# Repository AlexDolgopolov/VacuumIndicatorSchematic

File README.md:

<h1 align="center">Vacuum fluorescent clock</h1>
<h3 align="center">Vacuum fluorescent clock schematic and pcb. Drives with STM32F103 "BluePill". Driver code in progress.</h3>
<h4>Standart schematic for STM32F103 MCU. MCU pins connected to BJT's base with 4.7k resistors. VCC to heater and logic is 5V provided by external supply. I use the AP1117 LDO to make 
2.5 V heater voltage and VT1 for PWM the heater, drived from MCU. 3 button switches to provide user clock configuration, like setting timer or clock bright. Cathodes drived via npn BJT's.</h4>
<h2>
<h4>This scheme discribes anode drivers. I use +25 V Q=0.1..0.4 external voltage generator with simple schematic based on blocking genrator.
Schematic and PCB for this external generator will be added soon</h4>
<h2>
<h4>Connection between two PCB's realized by wires. If you open a PCB file in KiCAD, you can check the connections. Actually, it really doesn't matter how you connecting the wires, in STM32 driver you can remap the pins. But, PWM pins should be connected to heater.</h4>
<h2>
<h4>Thank you for watching this simple project. Work in progress now.</h4>

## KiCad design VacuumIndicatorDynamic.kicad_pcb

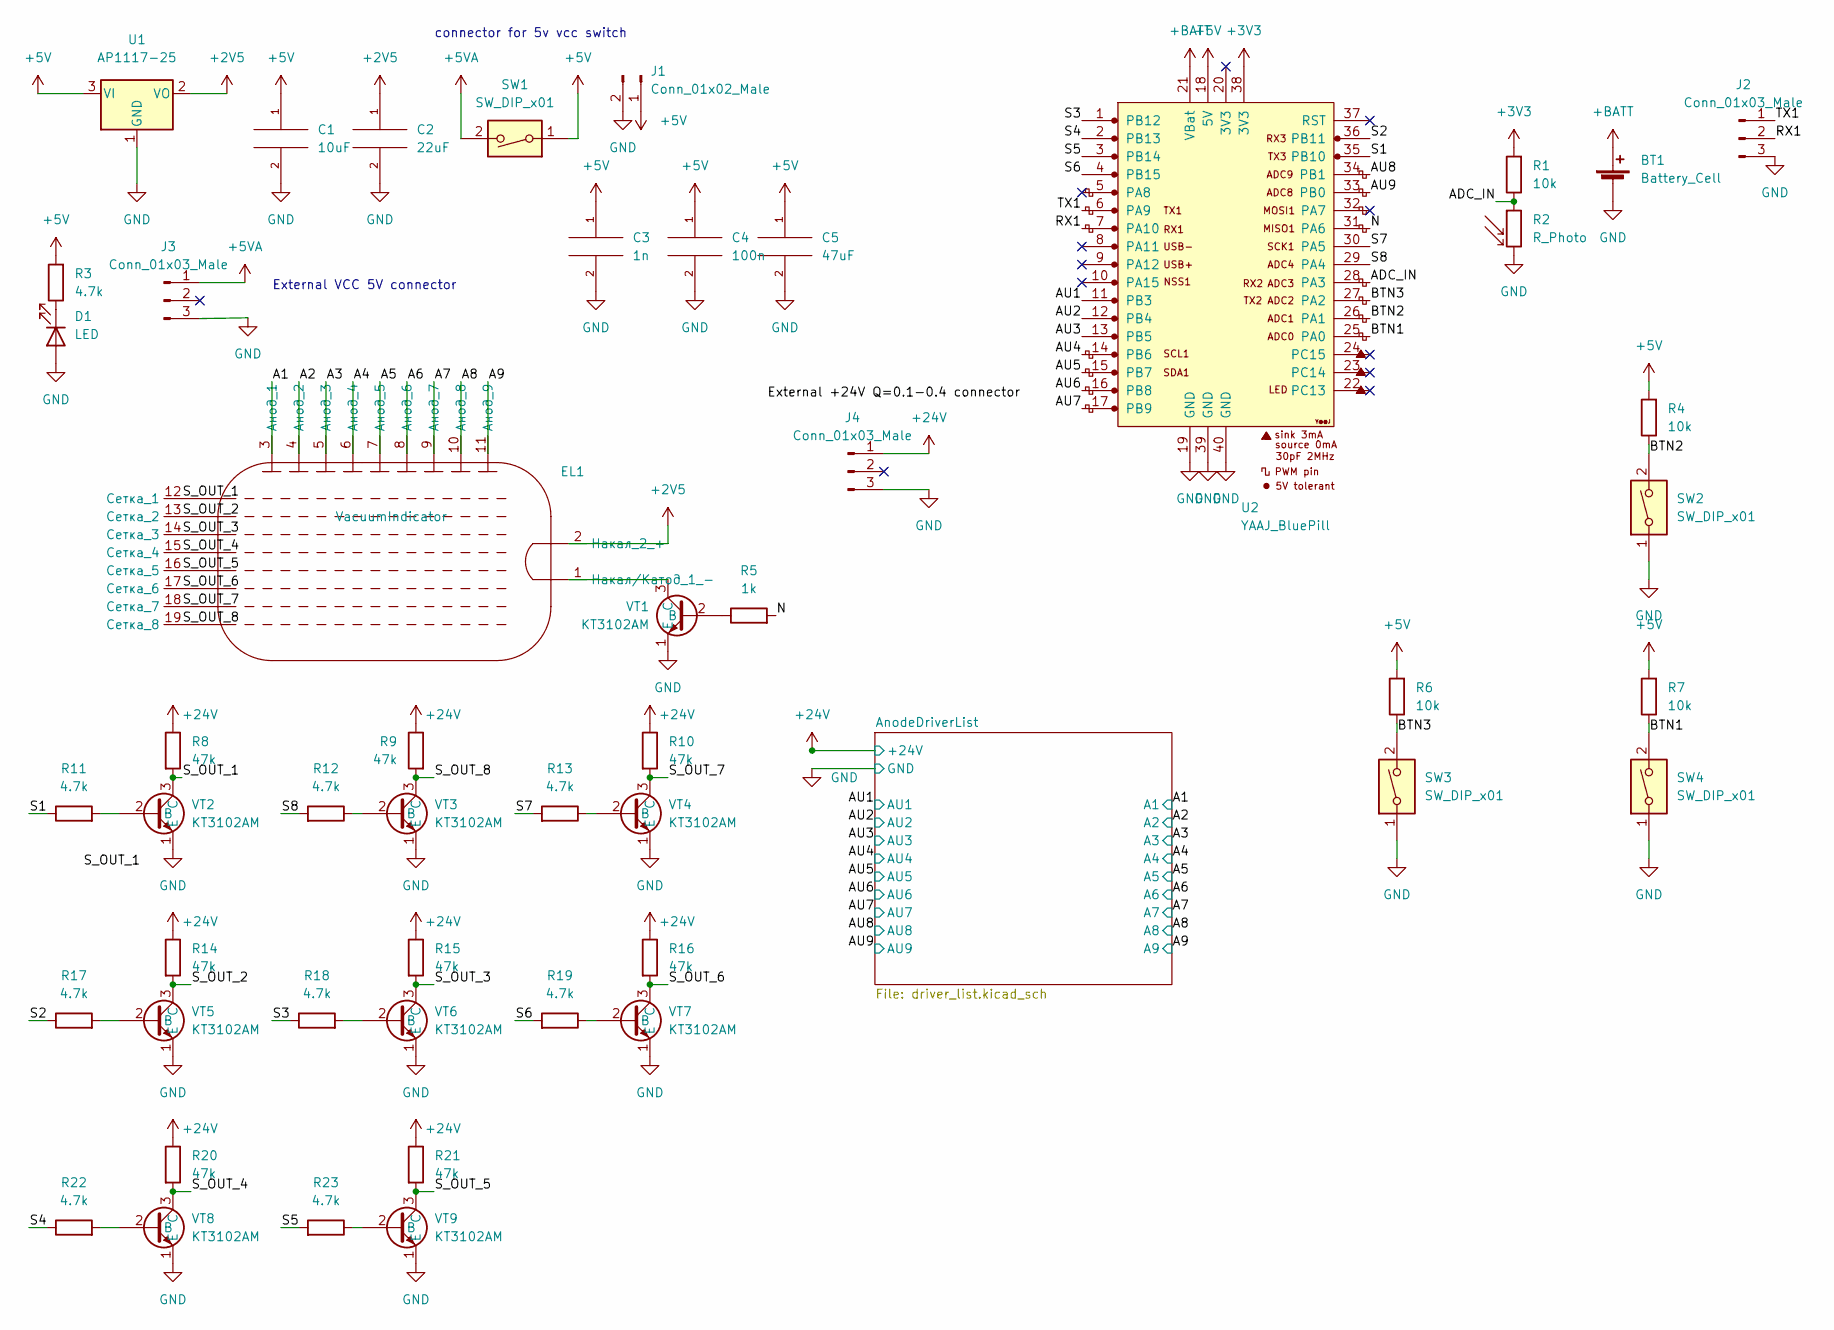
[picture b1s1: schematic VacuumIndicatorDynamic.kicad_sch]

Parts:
BT1: Battery_Cell; PinHeader_1x02_P2.54mm_Vertical
C1: 10uF; CP_Radial_D6.3mm_P2.50mm
C2: 22uF; CP_Radial_D6.3mm_P2.50mm
C3: 1n; C_0805_2012Metric
C4: 100n; C_0805_2012Metric
C5: 47uF; CP_Radial_D8.0mm_P5.00mm
D1: LED; LED_0805_2012Metric
EL1: VacuumIndicator; VauumIndicator_ILC_8-9
J1: Conn_01x02_Male; PinHeader_1x02_P2.54mm_Vertical
J2, J3, J4: Conn_01x03_Male; PinHeader_1x03_P2.54mm_Vertical
R1, R4, R6, R7: 10k; R_0805_2012Metric
R2: R_Photo; R_Axial_DIN0204_L3.6mm_D1.6mm_P1.90mm_Vertical
R3, R11, R12, R13, R17, R18, R19, R22, R23: 4.7k; R_0805_2012Metric
R5: 1k; R_0805_2012Metric
R8, R9, R10, R14, R15, R16, R20, R21: 47k; R_0805_2012Metric
SW1: SW_DIP_x01; PinSocket_1x02_P2.54mm_Vertical
SW2, SW3, SW4: SW_DIP_x01; SW_SPST_FSMSM
U1: AP1117-25; SOT-223-3_TabPin2
U2: YAAJ_BluePill; YAAJ_BluePill_1
VT1, VT2, VT3, VT4, VT5, VT6, VT7, VT8, VT9: KT3102AM; TO-92_HandSolder

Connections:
+2V5: C2.1, EL1.2 (Накал_2_+), U1.2 (VO)
+3V3: R1.2, U2.38 (3V3)
+5V: C1.1, C3.1, C4.1, C5.1, J1.1, R3.2, R4.2, R6.2, R7.2, SW1.1, U1.3 (VI), U2.18 (5V)
+5VA: J3.1, SW1.2
+24V: J4.1, R8.1, R9.1, R10.1, R14.1, R15.1, R16.1, R20.1, R21.1; also elsewhere on the board
+BATT: BT1.1 (+), U2.21 (VBat)
/A1: EL1.3 (Анод_1); also elsewhere on the board
/A2: EL1.4 (Анод_2); also elsewhere on the board
/A3: EL1.5 (Анод_3); also elsewhere on the board
/A4: EL1.6 (Анод_4); also elsewhere on the board
/A5: EL1.7 (Анод_5); also elsewhere on the board
/A6: EL1.8 (Анод_6); also elsewhere on the board
/A7: EL1.9 (Анод_7); also elsewhere on the board
/A8: EL1.10 (Анод_8); also elsewhere on the board
/A9: EL1.11 (Анод_9); also elsewhere on the board
/ADC_IN: R1.1, R2.1, U2.28 (PA3)
/AU1: U2.11 (PB3); also elsewhere on the board
/AU2: U2.12 (PB4); also elsewhere on the board
/AU3: U2.13 (PB5); also elsewhere on the board
/AU4: U2.14 (PB6); also elsewhere on the board
/AU5: U2.15 (PB7); also elsewhere on the board
/AU6: U2.16 (PB8); also elsewhere on the board
/AU7: U2.17 (PB9); also elsewhere on the board
/AU8: U2.34 (PB1); also elsewhere on the board
/AU9: U2.33 (PB0); also elsewhere on the board
/BTN1: R7.1, SW4.2, U2.25 (PA0)
/BTN2: R4.1, SW2.2, U2.26 (PA1)
/BTN3: R6.1, SW3.2, U2.27 (PA2)
/N: R5.2, U2.31 (PA6)
/RX1: J2.2, U2.7 (PA10)
/S1: R11.1, U2.35 (PB10)
/S2: R17.1, U2.36 (PB11)
/S3: R18.1, U2.1 (PB12)
/S4: R22.1, U2.2 (PB13)
/S5: R23.2, U2.3 (PB14)
/S6: R19.2, U2.4 (PB15)
/S7: R13.2, U2.30 (PA5)
/S8: R12.2, U2.29 (PA4)
/S_OUT_1: EL1.12 (Cетка_1), R8.2, VT2.3 (C)
/S_OUT_2: EL1.13 (Сетка_2), R14.2, VT5.3 (C)
/S_OUT_3: EL1.14 (Сетка_3), R15.2, VT6.3 (C)
/S_OUT_4: EL1.15 (Сетка_4), R20.2, VT8.3 (C)
/S_OUT_5: EL1.16 (Сетка_5), R21.2, VT9.3 (C)
/S_OUT_6: EL1.17 (Сетка_6), R16.2, VT7.3 (C)
/S_OUT_7: EL1.18 (Сетка_7), R10.2, VT4.3 (C)
/S_OUT_8: EL1.19 (Сетка_8), R9.2, VT3.3 (C)
/TX1: J2.1, U2.6 (PA9)
GND: BT1.2 (-), C1.2, C2.2, C3.2, C4.2, C5.2, D1.2 (A), J1.2, J2.3, J3.3, J4.3, R2.2, SW2.1, SW3.1, SW4.1, U1.1 (GND), U2.19 (GND), U2.39 (GND), U2.40 (GND), VT1.1 (E), VT2.1 (E), VT3.1 (E), VT4.1 (E), VT5.1 (E), VT6.1 (E), VT7.1 (E), VT8.1 (E), VT9.1 (E); also elsewhere on the board
unnamed: D1.1 (K), R3.1
unnamed: EL1.1 (Накал/Катод_1_-), VT1.3 (C)
unnamed: R5.1, VT1.2 (B)
unnamed: R11.2, VT2.2 (B)
unnamed: R12.1, VT3.2 (B)
unnamed: R13.1, VT4.2 (B)
unnamed: R17.2, VT5.2 (B)
unnamed: R18.2, VT6.2 (B)
unnamed: R19.1, VT7.2 (B)
unnamed: R22.2, VT8.2 (B)
unnamed: R23.1, VT9.2 (B)

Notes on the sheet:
External VCC 5V connector
connector for 5v vcc switch

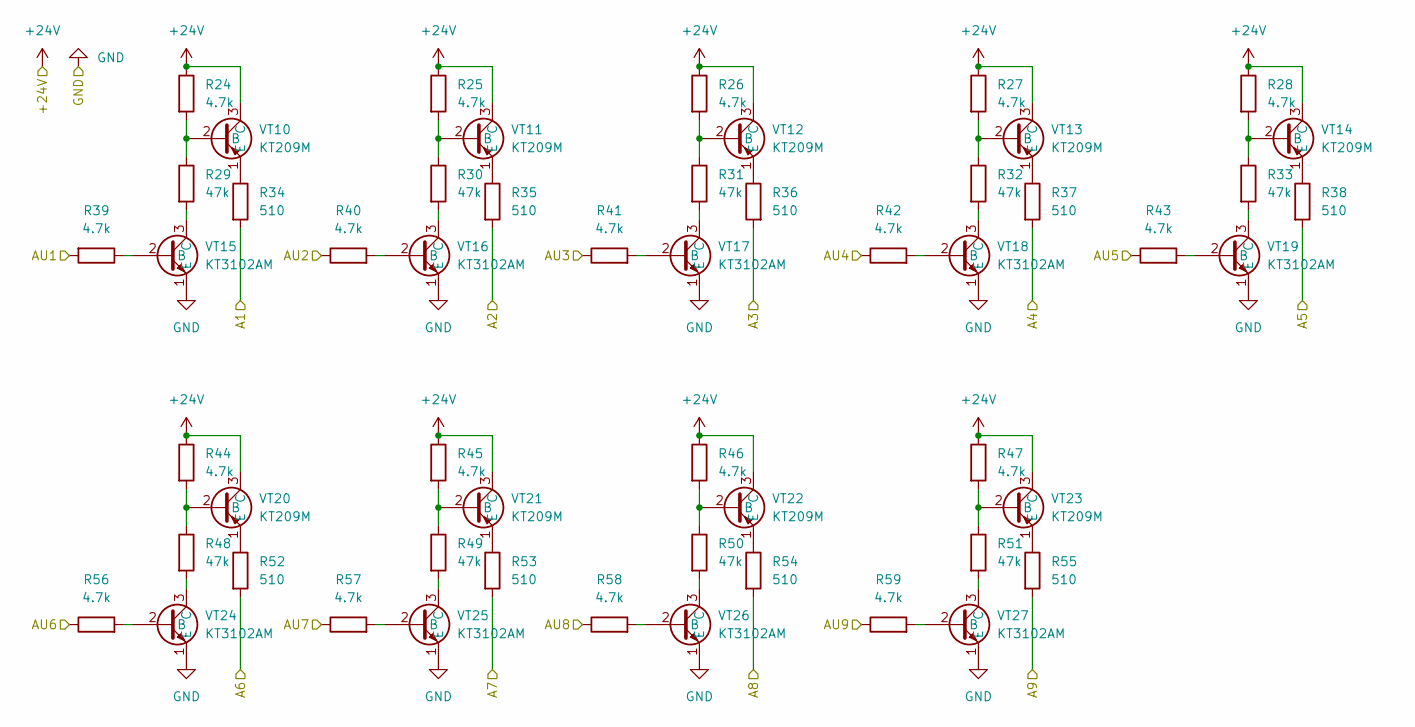
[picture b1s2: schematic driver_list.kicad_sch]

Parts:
R24, R25, R26, R27, R28, R39, R40, R41, R42, R43, R44, R45, R46, R47, R56, R57, R58, R59: 4.7k; R_0805_2012Metric
R29, R30, R31, R32, R33, R48, R49, R50, R51: 47k; R_0805_2012Metric
R34, R35, R36, R37, R38, R52, R53, R54, R55: 510; R_0805_2012Metric
VT10, VT11, VT12, VT13, VT14, VT20, VT21, VT22, VT23: КТ209М; TO-92_HandSolder
VT15, VT16, VT17, VT18, VT19, VT24, VT25, VT26, VT27: KT3102AM; TO-92_HandSolder

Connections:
+24V: R24.1, R25.1, R26.1, R27.1, R28.1, R44.1, R45.1, R46.1, R47.1, VT10.3 (C), VT11.3 (C), VT12.3 (C), VT13.3 (C), VT14.3 (C), VT20.3 (C), VT21.3 (C), VT22.3 (C), VT23.3 (C); also elsewhere on the board
/A1: R34.2; also elsewhere on the board
/A2: R35.2; also elsewhere on the board
/A3: R36.2; also elsewhere on the board
/A4: R37.2; also elsewhere on the board
/A5: R38.2; also elsewhere on the board
/A6: R52.2; also elsewhere on the board
/A7: R53.2; also elsewhere on the board
/A8: R54.2; also elsewhere on the board
/A9: R55.2; also elsewhere on the board
/AU1: R39.2; also elsewhere on the board
/AU2: R40.1; also elsewhere on the board
/AU3: R41.1; also elsewhere on the board
/AU4: R42.1; also elsewhere on the board
/AU5: R43.1; also elsewhere on the board
/AU6: R56.1; also elsewhere on the board
/AU7: R57.1; also elsewhere on the board
/AU8: R58.1; also elsewhere on the board
/AU9: R59.1; also elsewhere on the board
GND: VT15.1 (E), VT16.1 (E), VT17.1 (E), VT18.1 (E), VT19.1 (E), VT24.1 (E), VT25.1 (E), VT26.1 (E), VT27.1 (E); also elsewhere on the board
unnamed: R24.2, R29.1, VT10.2 (B)
unnamed: R25.2, R30.1, VT11.2 (B)
unnamed: R26.2, R31.1, VT12.2 (B)
unnamed: R27.2, R32.1, VT13.2 (B)
unnamed: R28.2, R33.1, VT14.2 (B)
unnamed: R29.2, VT15.3 (C)
unnamed: R30.2, VT16.3 (C)
unnamed: R31.2, VT17.3 (C)
unnamed: R32.2, VT18.3 (C)
unnamed: R33.2, VT19.3 (C)
unnamed: R34.1, VT10.1 (E)
unnamed: R35.1, VT11.1 (E)
unnamed: R36.1, VT12.1 (E)
unnamed: R37.1, VT13.1 (E)
unnamed: R38.1, VT14.1 (E)
unnamed: R39.1, VT15.2 (B)
unnamed: R40.2, VT16.2 (B)
unnamed: R41.2, VT17.2 (B)
unnamed: R42.2, VT18.2 (B)
unnamed: R43.2, VT19.2 (B)
unnamed: R44.2, R48.1, VT20.2 (B)
unnamed: R45.2, R49.1, VT21.2 (B)
unnamed: R46.2, R50.1, VT22.2 (B)
unnamed: R47.2, R51.1, VT23.2 (B)
unnamed: R48.2, VT24.3 (C)
unnamed: R49.2, VT25.3 (C)
unnamed: R50.2, VT26.3 (C)
unnamed: R51.2, VT27.3 (C)
unnamed: R52.1, VT20.1 (E)
unnamed: R53.1, VT21.1 (E)
unnamed: R54.1, VT22.1 (E)
unnamed: R55.1, VT23.1 (E)
unnamed: R56.2, VT24.2 (B)
unnamed: R57.2, VT25.2 (B)
unnamed: R58.2, VT26.2 (B)
unnamed: R59.2, VT27.2 (B)

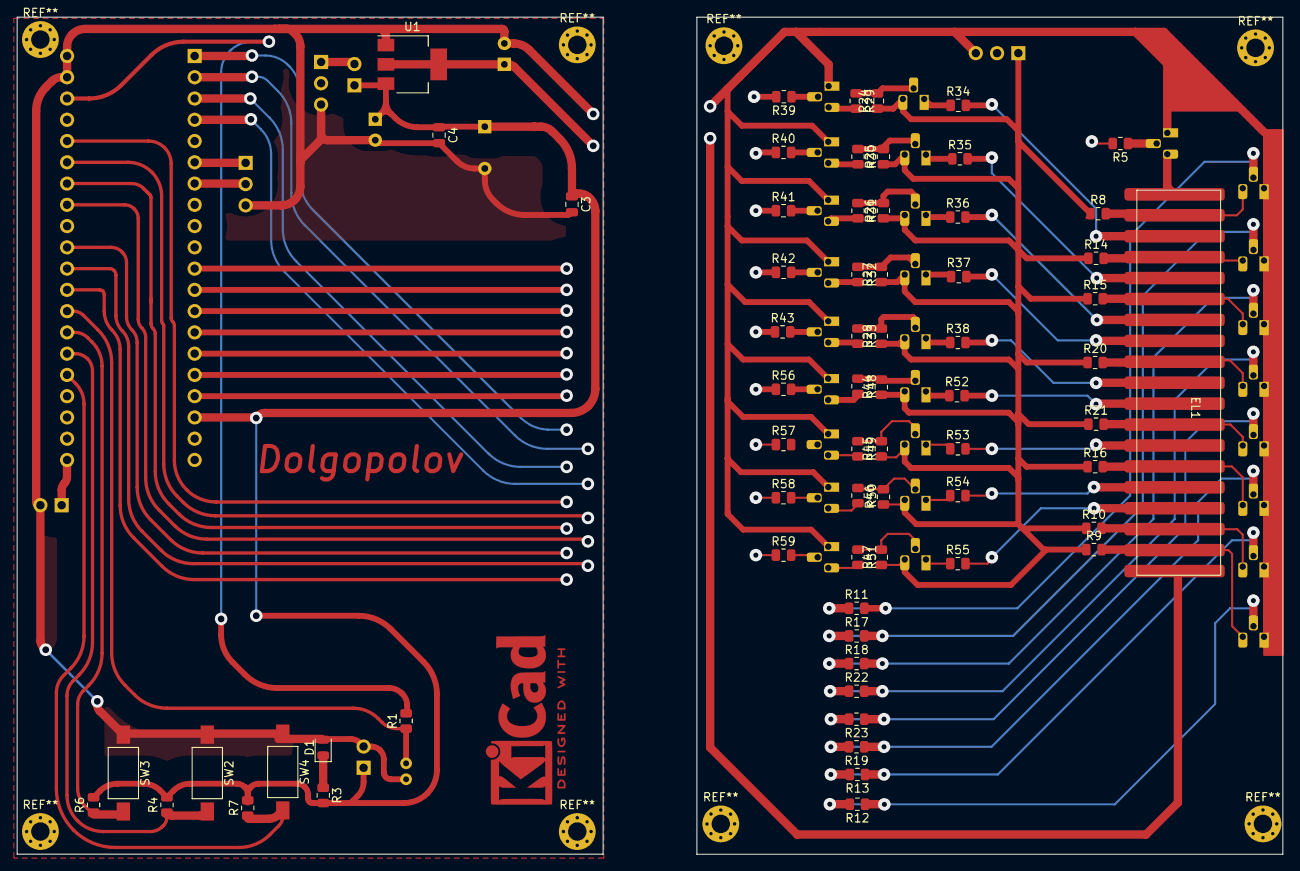
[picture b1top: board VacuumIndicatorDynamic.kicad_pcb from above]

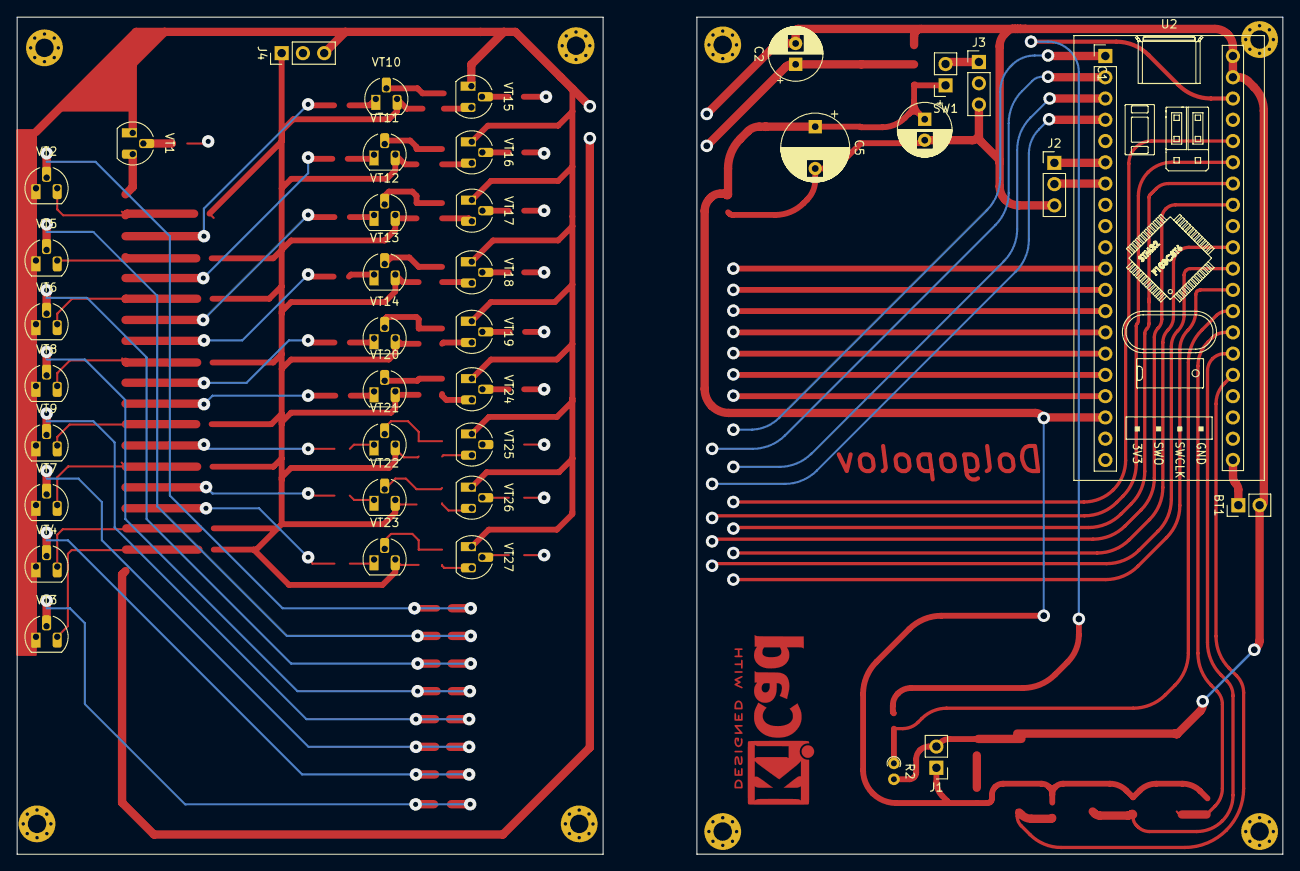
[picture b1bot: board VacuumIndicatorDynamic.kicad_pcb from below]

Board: 2 copper layers, 151.2 x 100.0 mm, 104 parts (38 on the bottom side), 95 nets.

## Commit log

2023-01-28 Изменения, которые будут включены в коммит: новый файл: ProjectLib.kicad_sym новый файл: ProjectLibrary.pretty/VauumIndicator_ILC_8-9.kicad_mod новый файл: ProjectLibrary.pretty/YAAJ_BluePill_1.kicad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
2023-01-29 update pcb
2023-01-29 pcb update. ready for fabrication
2023-01-31 Add mounting hole; remove copper area
2023-01-31 remove copper area add mounting holes
2023-02-02 several pcb updates
2023-02-02 make images
2023-02-03 major pcb update
2023-02-04 pcb route width update. add small copper area
2023-02-11 Remake sch after fabrication. Clear repo
